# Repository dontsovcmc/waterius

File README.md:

# Ватериус 2.0.56
## Wi-Fi приставка для импульсных счётчиков воды, газа, тепла

[Еnglish](https://github.com/dontsovcmc/waterius/blob/master/English.md)

✅ Протоколы HTTP, MQTT

✅ Поддержка <a href="https://yandex.ru/alice/smart-home" targe="_blank">Умного дома Яндекса</a>, <a href="https://www.home-assistant.io/" targe="_blank">HomeAssistant</a>,  <a href="https://www.hackster.io/dontsovcmc/domoticz-4346d5" targe="_blank">Domoticz</a>, <a href="https://spruthub.ru" targe="_blank">SprutHub</a> 

✅ Личный кабинет <a href="https://waterius.ru?utm_source=github&utm_medium=link&utm_campaign=github_16092021&utm_content=github&utm_term=github" target="_blank">waterius.ru</a>

- автоматическая <a href="https://waterius.ru?utm_source=github&utm_medium=link&utm_campaign=github_16092021&utm_content=github&utm_term=github" target="_blank">сдача показаний счётчиков</a> в 157 «водоканал» России и СНГ (на сентябрь 2025 г.).
- официальный партнер <a href="https://mos.ru" target="_blank">mos.ru</a>
- отправка на электронную почту
- отправка по СМС 
- телеграм бот

✅ Работает от 3-х батареек АА несколько лет

✅ [Тревоги](Alarms.md) (функции экспериментальные): много воды сразу, протечка, остановка расхода, датчик воды на полу

### Подходит к счётчикам
✅ Все счётчики воды с [импульсным выходом](https://github.com/dontsovcmc/waterius/issues/65) (провод торчит из корпуса)

✅ Все счётчики газа с герконом

✅ Электронные счётчики газа: Бетар СГБМ-4 [подробнее](https://github.com/dontsovcmc/waterius/issues/233)

✅ Электронные счётчики тепла: Sanext Monu CU, Берил ITELMA СТЭ 31 [подробнее](https://github.com/dontsovcmc/waterius/issues/233)

✅ Счётчики электричества: Энергомера CE101, Энергомера ЦЭ6803В 10-100А М7 Р31 и возможно другие импульсные.
Электронный вход проверен на 20 импульсах в секунду: этого хватает счётчику на 3200 имп/кВт·ч до 22 кВт (прошивка attiny 47 и новее)

### Где купить

[waterius.ru](https://waterius.ru?utm_source=github&utm_medium=link&utm_campaign=github_16092021&utm_content=github&utm_term=github)

### Характеристики
- подключение до двух счётчиков
- 3 АА батарейки (~2-4 года работы)
- передача по Wi-Fi
- не нужно знать, вес импульса у счётчика воды (Ватериус сам определит 1 или 10л/имп)
- не нужно знать, какого типа выход счётчика воды: "сухой контакт" или "НАМУР"
- настраиваемый период отправки
- [выход на связь только при расходе](Setup.md#выходить-на-связь-только-при-расходе): без расхода
  выходит на связь раз в 3 суток, по кнопке и тревоге — сразу
- [режим «Я уехал»](Alarms.md#режим-я-уехал): тревогой становится любой расход, пока вас нет дома
  (прошивка attiny 44 и новее)
- вместо счётчика к входу можно подключить [датчик протечки на полу](Alarms.md#датчик-протечки-на-полу):
  тревогой становится вода между электродами, а не только замыкание контактов (прошивка attiny 44 и новее)
- ручная настройка веса импульса
- дискавери для Home Assistant (есть и интеграция в HAOS)
- возможно указать свои: веб сервер, MQTT брокер, NTP сервер
- поддержка SprutHub
- поддержка WirenBoard

#### Данные с Ватериуса можно увидеть:
* на сайте <a href="https://waterius.ru?utm_source=github&utm_medium=link&utm_campaign=github_16092021&utm_content=github&utm_term=github">waterius.ru</a>
* в Приложении <a href="https://yandex.ru/alice/smart-home">Умный дом с Алисой от Яндекса</a>
* в HomeAssistant [инструкция с пояснениями](Home_Assistant_setup.md), [конфигурация](https://github.com/dontsovcmc/waterius/blob/master/homeassistant.configuration.yaml), [обсуждение](https://github.com/dontsovcmc/waterius/issues/86) или [интеграция](https://github.com/Anat0l/waterius-ha)
* в Domoticz [инструкция](https://www.hackster.io/dontsovcmc/domoticz-4346d5)
* в SprutHub [инструкция](https://wiki.spruthub.ru/%D0%A1%D0%BE%D0%B7%D0%B4%D0%B0%D0%BD%D0%B8%D0%B5_%D0%BA%D0%BE%D0%BD%D1%82%D1%80%D0%BE%D0%BB%D0%BB%D0%B5%D1%80%D0%B0_MQTT)
* на вашем [HTTP/HTTPS сервере](https://github.com/dontsovcmc/waterius/blob/master/Export.md#%D0%BD%D0%B0%D1%81%D1%82%D1%80%D0%BE%D0%B9%D0%BA%D0%B0-%D0%BE%D1%82%D0%BF%D1%80%D0%B0%D0%B2%D0%BA%D0%B8-%D0%BF%D0%BE-http-%D1%81%D0%B2%D0%BE%D0%B9-%D1%81%D0%B5%D1%80%D0%B2%D0%B5%D1%80)
* в MQTT клиенте [описание полей и настройка](https://github.com/dontsovcmc/waterius/blob/master/Export.md#настройка-отправки-по-mqtt)
* там, куда сами запрограммируете
  * [httpwaterius](https://github.com/grffio/httpwaterius) - web сервер с простым UI от [grffio](https://github.com/grffio)
* передать сразу в управляющую компанию через сайт [waterius.ru](https://waterius.ru?utm_source=github&utm_medium=link&utm_campaign=github_16092021&utm_content=github&utm_term=github).

## Подключение и настройка
[Текстом](http://waterius.ru/manual?utm_source=github)
[Видео](https://www.youtube.com/watch?v=dsmIdWbqJ58)

## Аналоги
[Заводские и DIY](https://github.com/dontsovcmc/waterius/issues/10)

## DIY Сделать самому
[Скачать прошивки](https://github.com/dontsovcmc/waterius/releases)

[Прошить ESP из браузера](https://waterius.github.io/update/): страница заливает скачанный `.bin` в ESP8266 по USB-TTL, без установки программ (Chrome или Edge)

[Обновить Ватериус 2 по воздуху](https://account.waterius.ru/update/) из личного кабинета: загрузите прошивку и файловую систему, обновление начнётся, когда устройство выйдет на связь

Бета-версия (сборка из ветки `dev`, для тех, кто готов проверять новое): [2.0.56-48-beta](https://github.com/dontsovcmc/waterius/releases/tag/2.0.56-48-beta)

Народная инструкция в инфо Телеграм чата: [waterius_forum](https://t.me/waterius_forum)
- [Список деталей и создание платы](https://github.com/dontsovcmc/waterius/blob/master/Making.md)
- [Прошивка Attiny85 и ESP](https://github.com/dontsovcmc/waterius/blob/master/Firmware.md) 
- [Установка и настройка](https://github.com/dontsovcmc/waterius/blob/master/Setup.md) 

### Геркон для газового счётчика
Корпус для геркона под газовый счетчик BK-G4T [bk-g4t-sensor.zip](https://github.com/dontsovcmc/waterius/files/10365883/bk-g4t-sensor.zip)

## Принцип работы
Счётчик импульсов состоит из двух микросхем. Attiny85 считает импульсы в режиме сна и сохраняет их в EEPROM. Раз в сутки она будит ESP8266 и слушает i2c линию. ESP8266 спрашивает у Attiny85 данные и отправляет их на сервер. После этого ESP8266 засыпает, а Attiny85 продолжает считать-считать-считать...

### Известные ошибки
- Иногда не надёжно подключается к некоторым роутера Asus, Kineetic. Укажите в настройках Вай-фая ватериуса "only G". 
- До версии 0.11.8: Иногда не подключается к Ростелекомовским роутерам: Sercomm rv6699, Innbox e70, e80 (192.168.0.1), TP-Link AX5400. Лечится указанием статического ip в настройках. Если у вас такие, напишите в теме: [Проблемы с роутерами](https://github.com/dontsovcmc/waterius/issues/131)
- До версии 0.11.7 не подключается к Wi-Fi с пробелом в названии.

## Схема
Заводская плата:

В репозитории ещё есть однослойная для ЛУТа.

## Разработка 
Ветка dev для pull-request
Ветка master только для публикации прошивок

**Симулятор портала** — страницы настройки открываются в браузере такими же, как на
устройстве, а импульсы, кнопка и Wi-Fi имитируются с пульта. Полезен, чтобы посмотреть
портал, не собирая прошивку: [simulator/README.md](simulator/README.md).

**Как устроена прошивка** — [docs/README.md](docs/README.md): счёт импульсов, расписание, отправка, тревоги, портал, OTA.

**Тесты:**
- бизнес-логика ЕСП на компьютере, без железа: `ESP8266/scripts/run_tests.sh`, attiny — `Attiny85/scripts/run_tests.sh`;
- стенд на живом железе: настоящий Ватериус, управляемая точка доступа и свой брокер — [Utils/hil/README.md](Utils/hil/README.md).

Из актуальных задач остались сложные:
- ~~Реализовать запись лога в файл (LittleFS), чтобы можно было скачать (/logs.html)~~ — решено: журнал портала в памяти скачивается со страницы «Логи» ([описание](docs/setup-portal.md#журнал-и-список-сетей))
- ~~OTA обновления: предложить код прошивки и пример веб-сервера~~ — решено в [2.0.43-beta](https://github.com/dontsovcmc/waterius/releases/tag/v.2.0.43-beta): Ватериус 2 обновляется по воздуху командой сервера или MQTT, из личного кабинета — на [странице обновления](https://account.waterius.ru/update/) ([описание](ESP8266/doc/ota.md))

### Модификации
[ветка attiny84](https://github.com/dontsovcmc/waterius/tree/attiny84) поддерживает плату [Waterius-Attiny84-ESP12F](https://github.com/badenbaden/Waterius-Attiny84-ESP12F) с 4мя счетчиками и 2мя датчиками протечек.

[Waterius на ESP32 с NB-IoT](https://github.com/OloloevReal/Waterius32) от OloloevReal

Датчик протечек:
- На пине reset сделал [OloloevReal](https://github.com/OloloevReal), вот [схема](https://github.com/dontsovcmc/waterius/issues/51)
- Есть в клоне [Waterius-Attiny84-ESP12F](https://github.com/badenbaden/Waterius-Attiny84-ESP12F), спасибо [badenbaden]

# Ответственность
Прошивка Ватериуса сделана на основе открытых библиотек, работоспособность которых никто не гарантирует. Я также не могу обещать, что устройство будет работать с вашем оборудованием и вы не получите ущерба как во время изготовления, так и во время эксплуатации устройства =). Пожалуйста, сообщите о любом опыте изготовления и использования [тут](https://github.com/dontsovcmc/waterius/issues). Вы поможете развитию проекта! 
[Лицензия GNU LGPLv3](https://github.com/dontsovcmc/waterius/blob/master/LICENSE)

# Благодарности
- [marvel-m9y](https://github.com/marvel-m9y) за поддержку HTTPS
- [OloloevReal](https://github.com/OloloevReal) за датчик протечки, работу по ESP32
- [popsodav](https://github.com/popsodav) за MQTT
- Ивану Коваленко и Иван Ганжа за консультации по электротехнике
- Alex Jensen, за проект [температурного датчика](https://www.cron.dk/esp8266-on-batteries-for-years-part-1).
- [freenetwork](https://github.com/freenetwork) за конфигурацию для HomeAssistant
- [grffio](https://github.com/grffio) за локальный веб-сервер
- [Игорю Вахромееву](http://vakhromeev.com) за наикрутейший редизайн настроек
- Сергею А. (г. Мурманск) за подробную инструкцию по [настройке Domoticz и NodeRed](https://www.hackster.io/dontsovcmc/domoticz-4346d5)
- [sintech](https://github.com/sintech) за найденные и исправленные баги
- [zinger76](https://github.com/zinger76) за ссылку на заказ платы и [3D модель крепления](https://github.com/dontsovcmc/waterius/blob/master/wall-mount/wall_mount.md) к стене
- [badenbaden](https://github.com/badenbaden) за дельные комментарии по производству и новую версию!
- [kick2nick](https://github.com/kick2nick) за доработки функционала.
- [foxel](https://github.com/foxel) за доработку платы.
- Пользователям, приславшим очепятки и предложения: Дмитрию (г. Москва), Сергею (г. Кострома), Александру (г. Санкт-Петербург), Сергею (г. Мурманск), Антону (г. Красноярск) и др.
- Денису С. (г. Москва) за видео установки Ватериуса.
- [ivakorin](https://github.com/ivakorin) за инструкцию к Home Assistant
- Евгению К. из Самары, Олегу из Москвы за критику и помощь с прошивкой
- Олегу К. из Республики Беларусь за [инструкцию к MajorDoMo](https://mjdm.ru/forum/viewtopic.php?p=129000#p129000)
- [Drafteed](https://github.com/Drafteed) за виджет карты России
- [neitri](https://github.com/neitri) за доработки прошивки
- [L2jLiga](https://github.com/L2jLiga) за обновление конфигурации Home Assistant
- nyroux за корпус геркона для газового счётчика
- Anat0liyBM за поддержку discovery HA
- [vzagorovskiy](https://github.com/vzagorovskiy) за большое обновление [0.11.0](https://github.com/dontsovcmc/waterius/releases/tag/0.11.0-beta)
- [abrant-ru](https://github.com/abrant-ru) за поддержку счётчиков с выходом "открытый коллектор" (короткими импульсами)
- Даниилу Макарову за дизайн веб интерфейса
- [videlinagbm](https://github.com/videlinagbm) за верстку веб интерфейса и js код
- [Anat0l](https://github.com/Anat0l/waterius-ha) за написание интеграции в HA

Форумам: 
- https://electronix.ru
- https://esp8266.ru
- https://easyelectronics.ru

## Star History

## Контакты

Связь: [Facebook](https://www.facebook.com/waterius), [VK](https://vk.com/waterius1), [Instagram](https://www.instagram.com/waterius.ru/)

Задавайте вопросы в Телеграм чате: [waterius_forum](https://t.me/waterius_forum)

Найденные ошибки [в issues](https://github.com/dontsovcmc/waterius/issues)

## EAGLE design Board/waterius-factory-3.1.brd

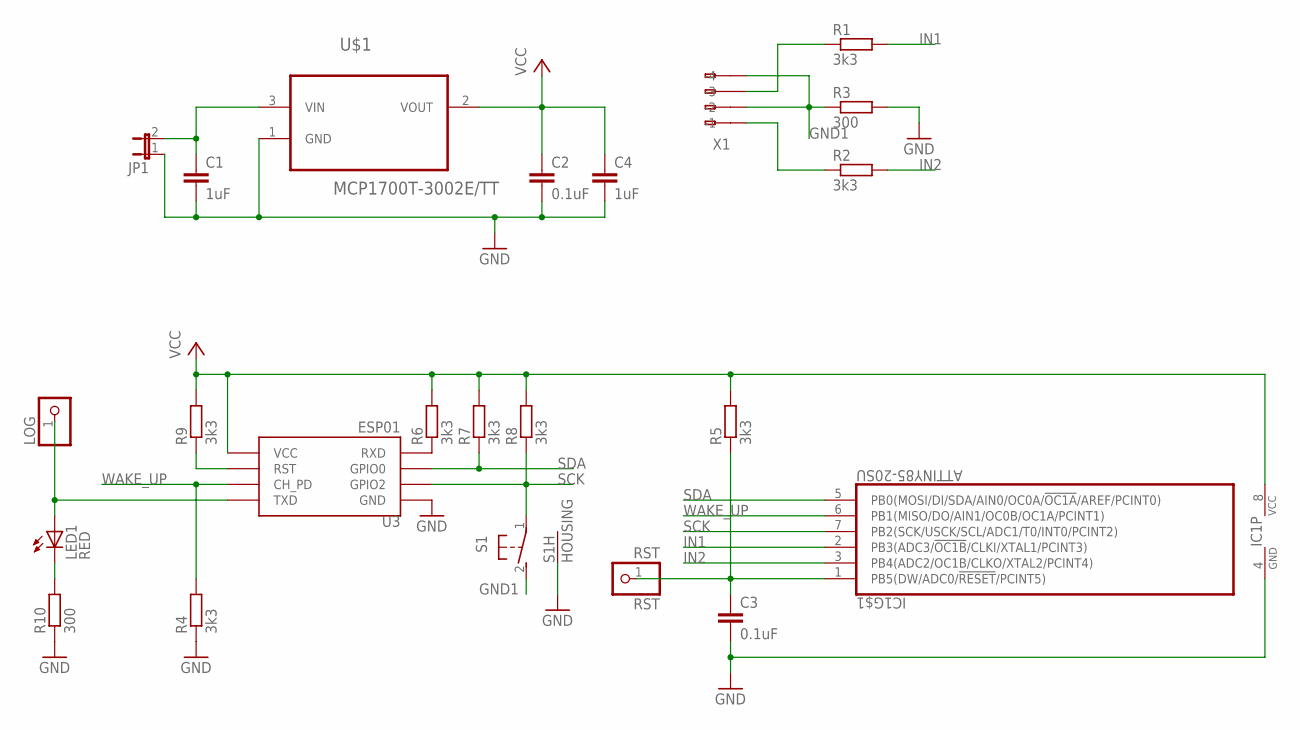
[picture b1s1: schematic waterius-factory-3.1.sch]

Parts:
C1, C4: 1uF; C0805
C2, C3: 0.1uF; C0805
IC1: ATTINY85-20SU; 8S2
JP1: JP1E; JP1
LED1: RED; LED3MM
LOG: PINHD-1X1; 1X01
R1, R2, R4, R5, R6, R7, R8, R9: 3k3; R0805
R3, R10: 300; R0805
RST: RST; 1X01
S1: 31-XX; B3F-31XX
U3: ESP01
U$1: MCP1700T-3002E/TT; SOT95P237X112-3N
X1: 233-104

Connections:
+3V: C2.1, C4.1, IC1.8 (VCC), R5.2, R6.2, R7.2, R8.2, R9.2, U3.VCC, U$1.2 (VOUT)
GND: C1.2, C2.2, C3.2, C4.2, IC1.4 (GND), JP1.1, R3.2, R4.1, R10.1, S1.3 (HOUSING), S1.4 (HOUSING), U3.GND, U$1.1 (GND)
GND1: R3.1, S1.2 (S), X1.A2 (-2), X1.A4 (-4)
IN1: IC1.2 (PB3(ADC3/!OC1B!/CLKI/XTAL1/PCINT3)), R1.2
IN2: IC1.3 (PB4(ADC2/OC1B/CLKO/XTAL2/PCINT4)), R2.2
unnamed: R6.1, U3.RX (RXD)
unnamed: R9.1, U3.RST
unnamed: LED1.A, LOG.1, U3.TX (TXD)
unnamed: LED1.K (C), R10.2
unnamed: R1.1, X1.A3 (-3)
unnamed: R2.1, X1.A1 (-1)
PRG_RST: C3.1, IC1.1 (PB5(DW/ADC0/!RESET!/PCINT5)), R5.1, RST.1
SCK: IC1.7 (PB2(SCK/USCK/SCL/ADC1/T0/INT0/PCINT2)), R8.1, S1.1, U3.GPIO2
SDA: IC1.5 (PB0(MOSI/DI/SDA/AIN0/OC0A/!OC1A!/AREF/P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), R7.1, U3.GPIO0
VBAT: C1.1, JP1.2, U$1.3 (VIN)
WAKE_UP: IC1.6 (PB1(MISO/DO/AIN1/OC0B/OC1A/PCINT1)), R4.2, U3.CH_PD

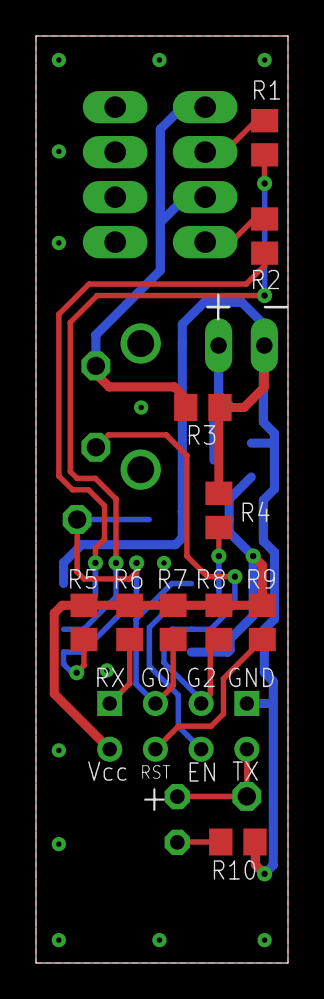
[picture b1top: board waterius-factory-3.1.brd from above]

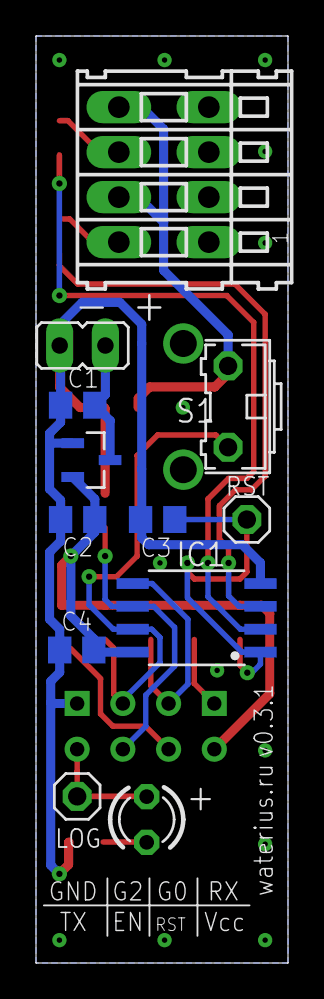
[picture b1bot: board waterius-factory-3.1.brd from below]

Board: 2 copper layers, 14.0 x 51.5 mm, 23 parts (13 on the bottom side), 16 nets.

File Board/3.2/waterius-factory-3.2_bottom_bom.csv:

Comment,Data,Designator,Footprint
CC0805KRX7R9BB104,0.1uF,C2 C3,C0805
CL21B105KBFNNNE,1uF,C1 C4,C0805
RC0805FR-073K3L,3k3,R1 R2 R4 R5 R6 R7 R8 R9,R0805
RC0805FR-07330RL,300,R3 R10,R0805
ATTINY85-20SU,ATTINY85-20SU,IC1,8S2
MCP1700T-3002E/TT,MCP1700T-3002E/TT,U$1,SOT95P237X112-3N

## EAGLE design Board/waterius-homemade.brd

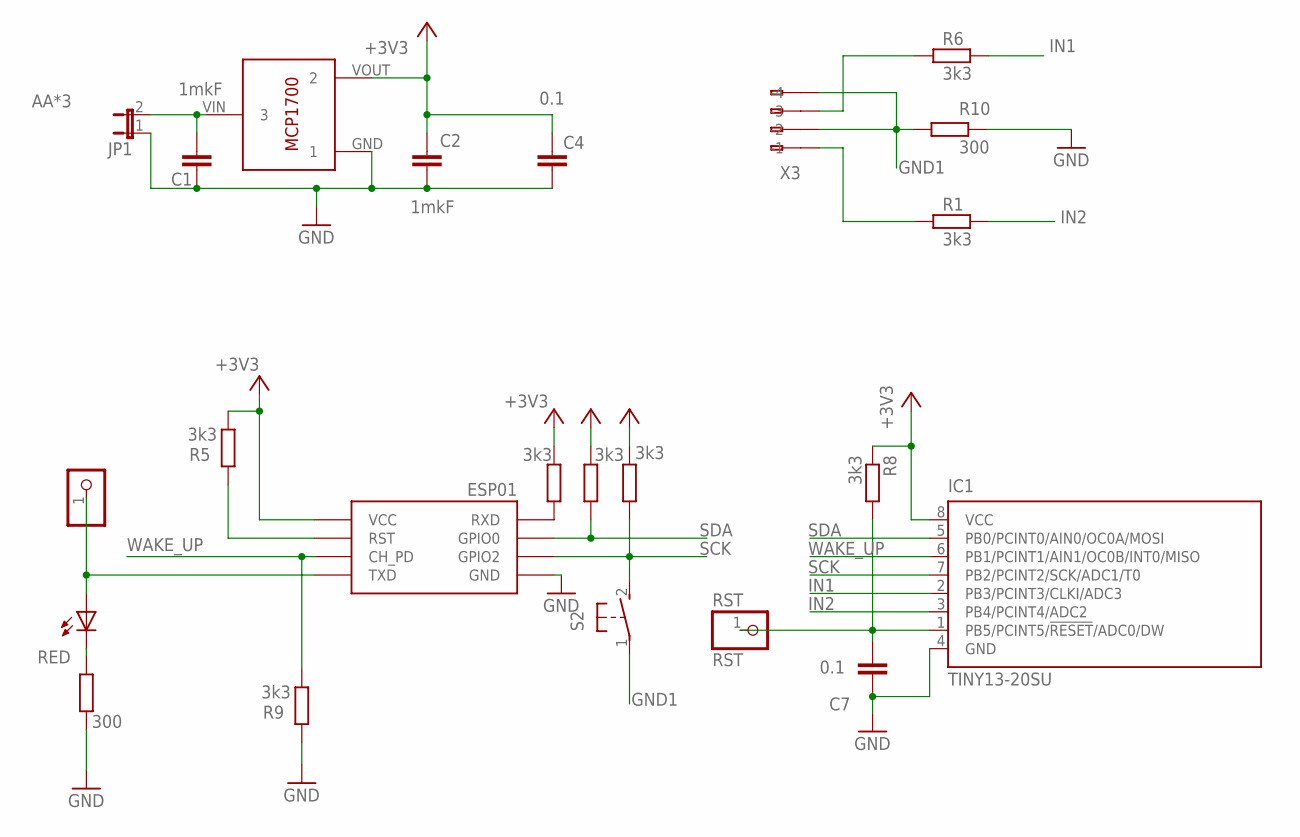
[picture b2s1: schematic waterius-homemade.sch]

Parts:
C1, C2: 1mkF; C0805
C4, C7: 0.1; C0805
IC1: TINY13-20SU; 8S2
JP1: JP1E; JP1
LED1: RED; LED3MM
LOG: LOG; 1X01
R1, R6: 3k3; M0805
R2, R3, R5, R7, R8, R9: 3k3; R0805
R4: 300; R0805
R10: 300; M0805
RST: RST; 1X01
S2: 31-XX; B3F-31XX
U$1: ESP01
U$2: MCP1700T-3302E/TT
X3: 233-104

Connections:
+3V3: C2.1, C4.1, IC1.8 (VCC), R2.1, R3.1, R5.1, R7.1, R8.1, U$1.VCC, U$2.VOUT (2)
AA*3: C1.1, JP1.2, U$2.VIN (3)
GND: C1.2, C2.2, C4.2, C7.1, IC1.4 (GND), JP1.1, R4.2, R9.2, R10.2, U$1.GND, U$2.GND (1)
GND1: R10.1, S2.1, X3.A2 (-2), X3.A4 (-4)
IN1: IC1.2 (PB3/PCINT3/CLKI/ADC3), R6.2
IN2: IC1.3 (PB4/PCINT4/ADC2), R1.2
unnamed: LED1.A, LOG.1, U$1.TX (TXD)
unnamed: R6.1, X3.A3 (-3)
unnamed: R1.1, X3.A1 (-1)
unnamed: LED1.K (C), R4.1
unnamed: R5.2, U$1.RST
unnamed: C7.2, IC1.1 (PB5/PCINT5/!RESET!/ADC0/DW), R8.2, RST.1
RX: R7.2, U$1.RX (RXD)
SCK: IC1.7 (PB2/PCINT2/SCK/ADC1/T0), R2.2, S2.2 (S), U$1.GPIO2
SDA: IC1.5 (PB0/PCINT0/AIN0/OC0A/MOSI), R3.2, U$1.GPIO0
WAKE_UP: IC1.6 (PB1/PCINT1/AIN1/OC0B/INT0/MISO), R9.1, U$1.CH_PD

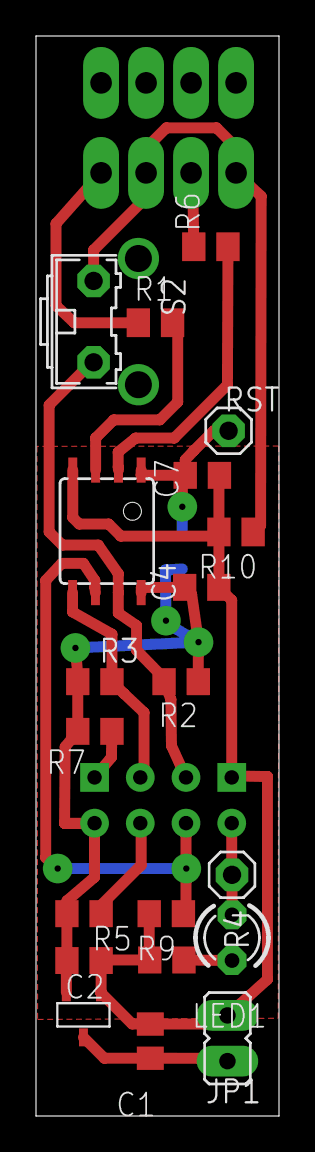
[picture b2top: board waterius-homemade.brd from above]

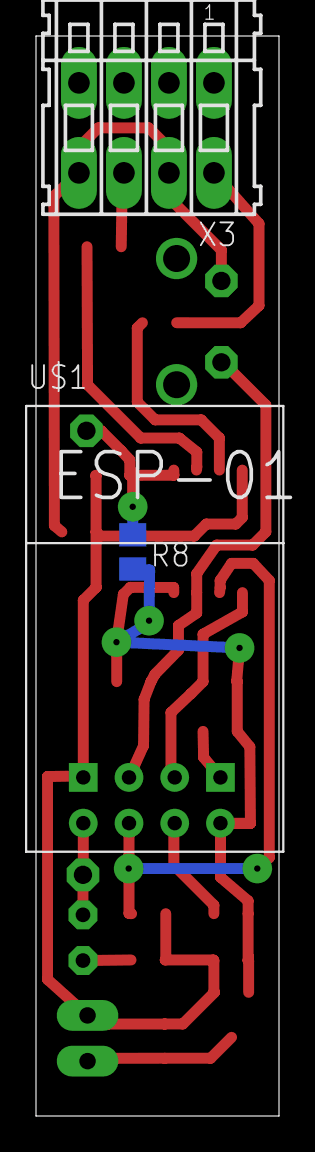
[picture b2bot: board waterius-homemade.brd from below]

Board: 2 copper layers, 13.5 x 60.0 mm, 23 parts (3 on the bottom side), 16 nets.

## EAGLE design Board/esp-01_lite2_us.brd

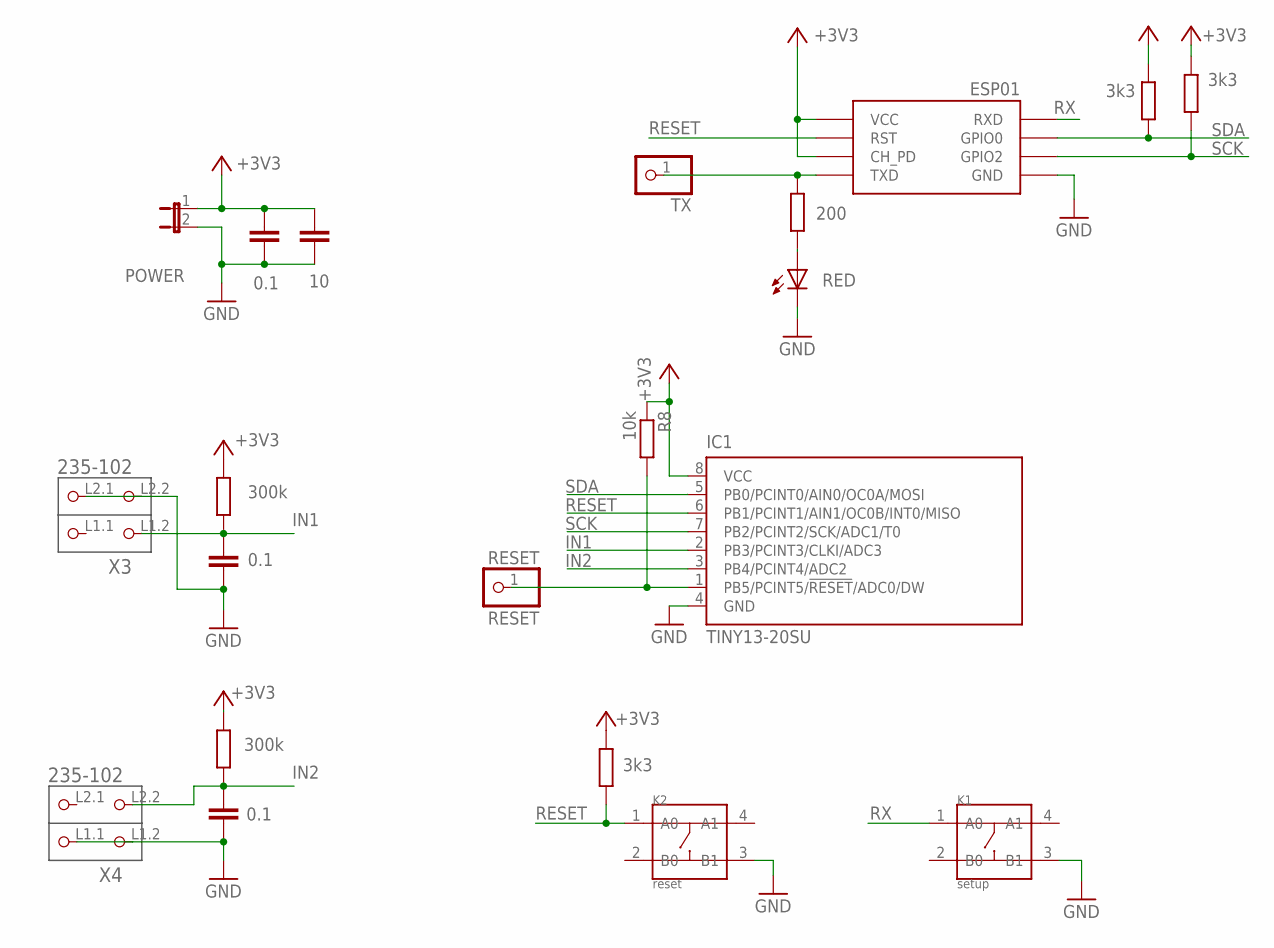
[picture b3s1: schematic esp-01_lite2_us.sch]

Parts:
C1, C2, C3: 0.1; C0805
C4: 10; C025-024X044
IC1: TINY13-20SU; 8S2
JP2: POWER; JP1
K1: setup; SW4-6.0X6.0X5.0MM
K2: reset; SW4-6.0X6.0X5.0MM
LED1: RED; SML0805
R2, R5: 3k3; R0805
R3: 3k3; 0207/5V
R4: 200; 0207/5V
R8: 10k; R0805
R10: 300k; R0805
R11: 300k; 0207/7
RESET: RESET; 1X01
TX: TX; 1X01
U$1: ESP01
X3, X4: 235-102; P-235-102

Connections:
+3V3: C3.1, C4.1, IC1.8 (VCC), JP2.1, R2.1, R3.1, R5.1, R8.1, R10.1, R11.1, U$1.CH_PD, U$1.VCC
GND: C1.2, C2.1, C3.2, C4.2, IC1.4 (GND), JP2.2, K1.3 (B1), K2.3 (B1), LED1.C, U$1.GND, X3.L2.1 (P2.1), X3.L2.2 (P2.2), X4.L1.1 (P1.1), X4.L1.2 (P1.2)
IN1: C1.1, IC1.2 (PB3/PCINT3/CLKI/ADC3), R10.2, X3.L1.2 (P1.2)
IN2: C2.2, IC1.3 (PB4/PCINT4/ADC2), R11.2, X4.L2.2 (P2.2)
unnamed: R4.1, TX.1, U$1.TX (TXD)
unnamed: LED1.A, R4.2
unnamed: IC1.1 (PB5/PCINT5/!RESET!/ADC0/DW), R8.2, RESET.1
RESET: IC1.6 (PB1/PCINT1/AIN1/OC0B/INT0/MISO), K2.1 (A0), R5.2, U$1.RST
RX: K1.1 (A0), U$1.RX (RXD)
SCK: IC1.7 (PB2/PCINT2/SCK/ADC1/T0), R2.2, U$1.GPIO2
SDA: IC1.5 (PB0/PCINT0/AIN0/OC0A/MOSI), R3.2, U$1.GPIO0

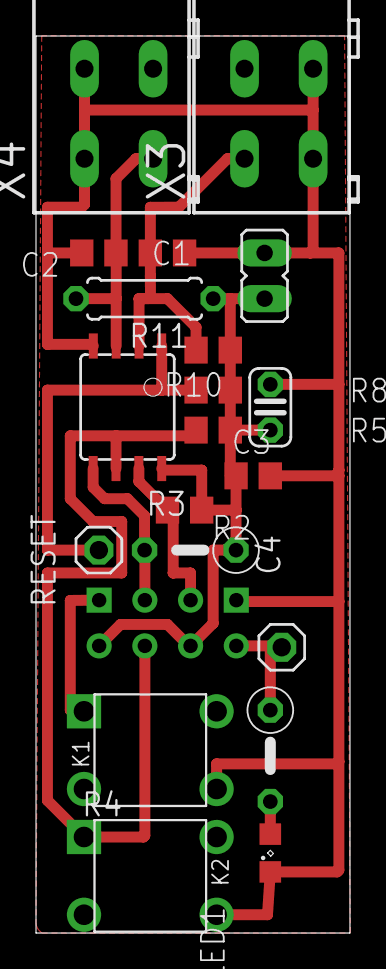
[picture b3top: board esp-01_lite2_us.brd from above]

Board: 1 copper layer, 17.4 x 49.8 mm, 21 parts (1 on the bottom side), 11 nets.

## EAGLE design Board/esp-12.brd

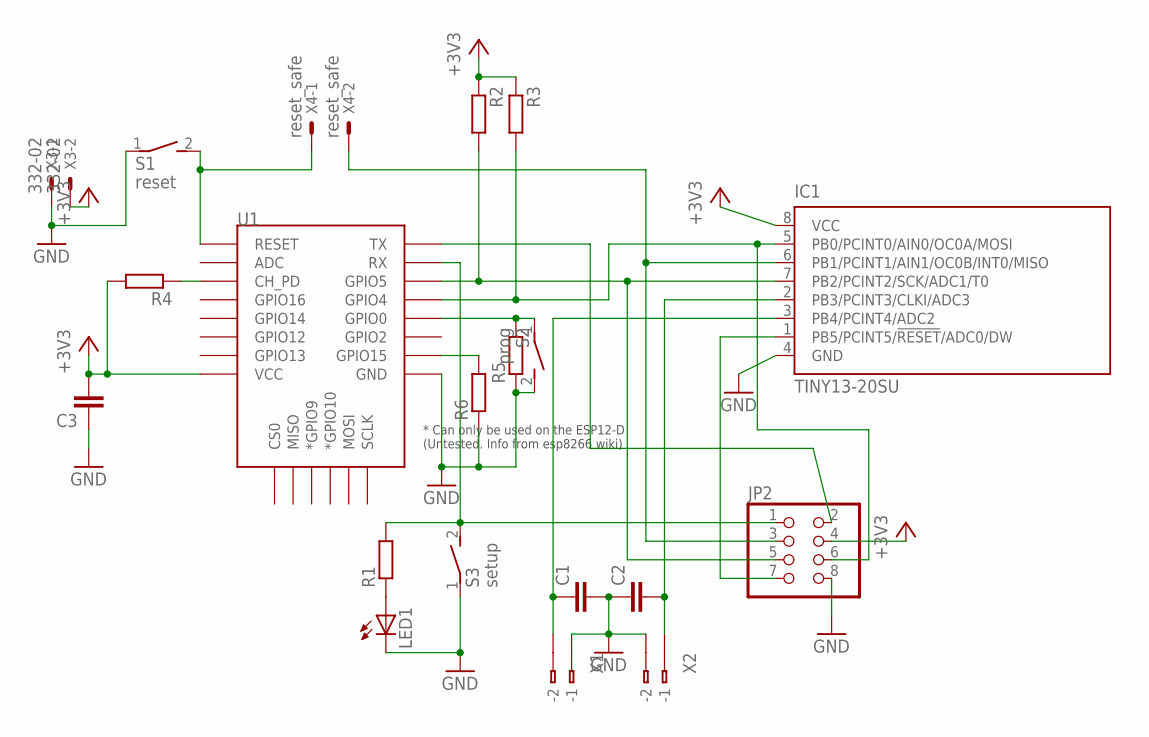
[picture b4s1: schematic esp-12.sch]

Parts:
C1, C2, C3: C-EUC0805; C0805
IC1: TINY13-20SU; 8S2
JP2: PINHD-2X4; 2X04
LED1: LEDSQR2X5; LED2X5
R1, R2, R3, R4, R5, R6: R-EU_R0805; R0805
S1: reset; DS-01
S2: prog; DS-01
S3: setup; DS-01
U1: ESP12ESMD; ESP12E-SMD
X1, X2: 233-102
X3: 332-02
X4: reset_safe; 332-02

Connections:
+3V3: C3.2, IC1.8 (VCC), JP2.4, R2.1, R3.1, R4.2, U1.VCC, X3.2
GND: C1.2, C2.1, C3.1, IC1.4 (GND), JP2.8, LED1.K (C), R5.1, R6.1, S1.1, S2.2, S3.1, U1.GND, X1.B1 (B-1), X2.B2 (B-2), X3.1
unnamed: IC1.7 (PB2/PCINT2/SCK/ADC1/T0), JP2.5, R2.2, U1.GPIO5
unnamed: IC1.5 (PB0/PCINT0/AIN0/OC0A/MOSI), JP2.6, R3.2, U1.GPIO4
unnamed: R5.2, S2.1, U1.GPIO0
unnamed: R6.2, U1.GPIO15
unnamed: IC1.1 (PB5/PCINT5/!RESET!/ADC0/DW), JP2.7
unnamed: C2.2, IC1.2 (PB3/PCINT3/CLKI/ADC3), X2.B1 (B-1)
unnamed: IC1.6 (PB1/PCINT1/AIN1/OC0B/INT0/MISO), JP2.3, X4.2
unnamed: C1.1, IC1.3 (PB4/PCINT4/ADC2), X1.B2 (B-2)
unnamed: S1.2, U1.RESET, X4.1
unnamed: LED1.A, R1.1
unnamed: JP2.2, U1.TXD0 (TX)
unnamed: JP2.1, R1.2, S3.2, U1.RXD0 (RX)
unnamed: R4.1, U1.CH_PD

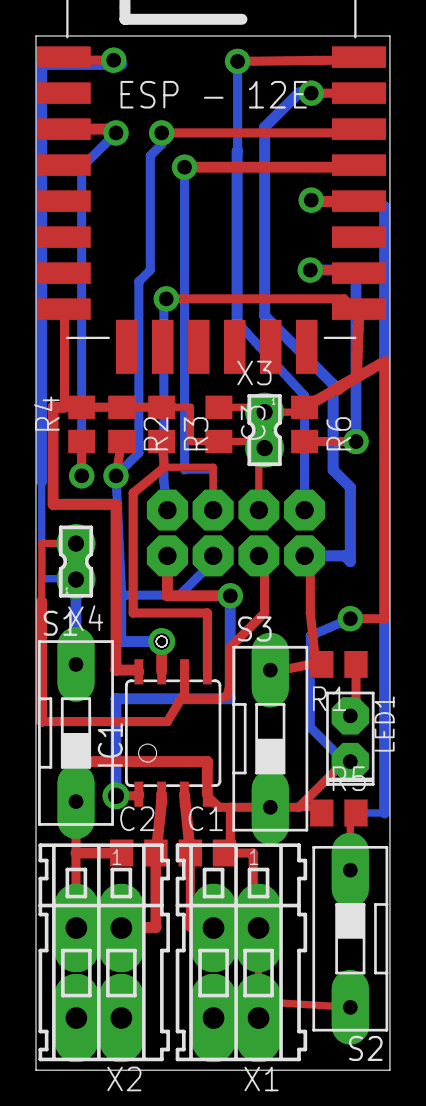
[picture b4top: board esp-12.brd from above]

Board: 2 copper layers, 19.7 x 57.5 mm, 20 parts (1 on the bottom side), 15 nets.

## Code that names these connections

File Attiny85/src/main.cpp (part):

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// Waterius Classic: https://github.com/dontsovcmc/waterius
//
//                                +-\/-+
//       RESET   (D  5/A0)  PB5  1|    |8  VCC
//  *Counter1*   (D  3/A3)  PB3  2|    |7  PB2  (D  2/ A1)         SCL   *Button*
//  *Counter0*   (D  4/A2)  PB4  3|    |6  PB1  (D  1)      MISO         *Power ESP*
//                          GND  4|    |5  PB0  (D  0)      MOSI   SDA
//                                +----+
//
// https://github.com/SpenceKonde/ATTinyCore/blob/master/avr/extras/ATtiny_x5.md

static CounterB counter0(4, 2); 	// Вход 1, Blynk: V0, горячая вода PB4 ADC2
static CounterB counter1(3, 3); 	// Вход 2, Blynk: V1, холодная вода (или лог) PB3 ADC3

static ESPPowerPin esp(1); // Питание на ESP

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static uint8_t alarm_hold_min = 0;

#if WATERIUS_MODEL == WATERIUS_MODEL_1
static ButtonB button(2);  // PB2 кнопка (на линии SCL)
                           // Долгое нажатие: ESP включает точку доступа с веб сервером для настройки
                           // Короткое: ESP передает показания
#endif
#if WATERIUS_MODEL == WATERIUS_MODEL_2
static ButtonB2 button(1);  // PB1 кнопка (на линии wakeup)
                           // Долгое нажатие: ESP включает точку доступа с веб сервером для настройки
                           // Короткое: ESP передает показания
#endif
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
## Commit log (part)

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2026-04-13 eeprom_parser
2026-04-14 обновил форматирование
2026-04-14 Установка через пакеты менеджер winget для пользователей windows 11
2026-06-02 attiny v.38 - 250ms+50ms = impulse
2026-06-02 gitignore
2026-06-03 some brainstorming
